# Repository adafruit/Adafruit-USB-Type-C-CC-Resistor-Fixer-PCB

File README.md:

## Adafruit USB Type C CC Resistor Fixer PCB

<a href="http://www.adafruit.com/products/6323"><br/>
Click here to purchase one from the Adafruit shop</a>

PCB files for the Adafruit USB Type C CC Resistor Fixer. 

Format is EagleCAD schematic and board layout
* https://www.adafruit.com/product/6323

### Description

Do you have any devices with USB C connections that don't seem to power or work when plugged into another USB C port? Chances are, the designers skimped a few pennies or just forgot to put in the two 5.1K CC resistors required for C-to-C connections at 5V. It can drive you batty because some computers care and some don't!

That's why we designed the Adafruit USB Type C CC Resistor Fixer, a collab between our  sunken USB socket and USB Plug breakout. It's the only product we hope we can discontinue one day, sooner rather than later! This small PCB assembly fits onto a cable or into the mis-designed port. It passes through the two data pins and the Vbus and Ground power lines, while adding the missing 5.1K resistors on the port side and a power good LED.

Note that the USB plug pinout doesn't carry the sideband wires or the high speed pins, so this is good for USB charge/sync but not for high speed or specialty protocols. If you're not sure, then it's very unlikely you need them: those products aren't going to mess up the CC resistors.

### License

Adafruit invests time and resources providing this open source design, please support Adafruit and open-source hardware by purchasing products from [Adafruit](https://www.adafruit.com)!

Designed by Limor Fried/Ladyada for Adafruit Industries.

Creative Commons Attribution/Share-Alike, all text above must be included in any redistribution. 
See license.txt for additional details.

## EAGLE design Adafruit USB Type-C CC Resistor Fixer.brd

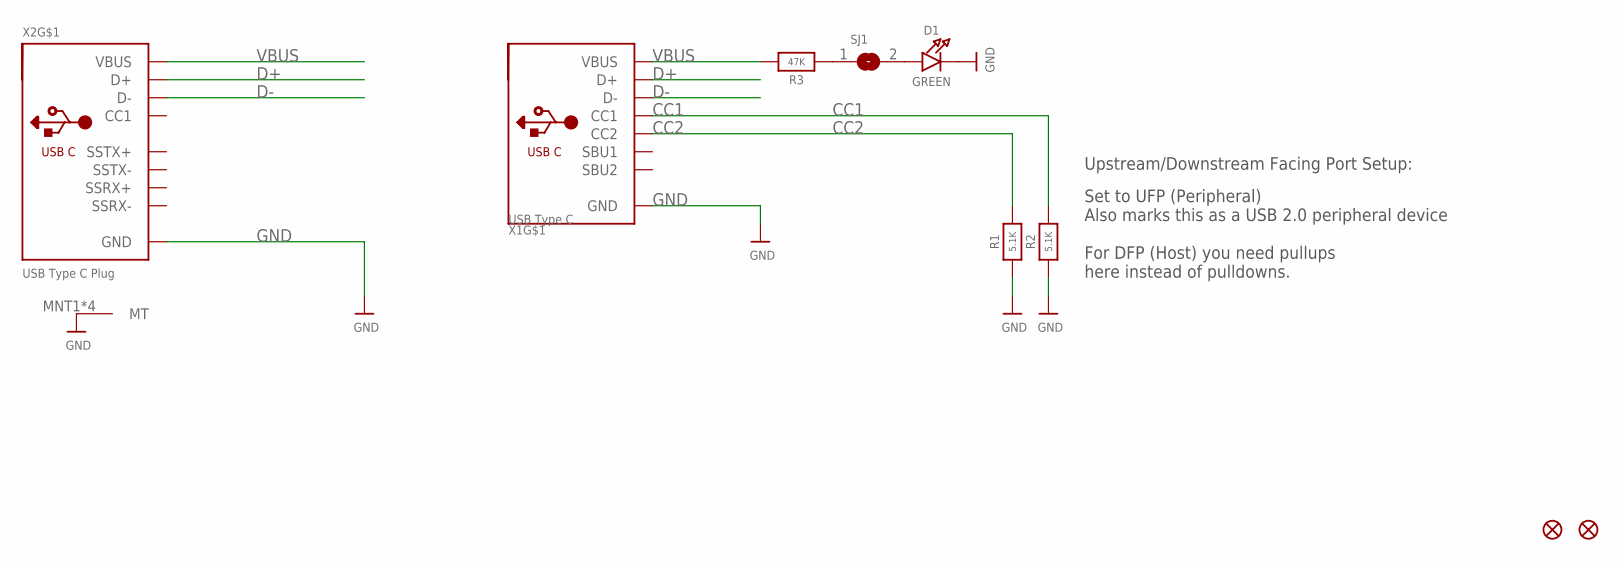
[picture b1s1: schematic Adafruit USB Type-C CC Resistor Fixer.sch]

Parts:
D1: GREEN; CHIPLED_0603_NOOUTLINE
FID1, FID2: FIDUCIAL_0.5MM
R1, R2: 5.1K; 0603-NO
R3: 47K; 0603-NO
SJ1: SOLDERJUMPERCLOSED; SOLDERJUMPER_CLOSEDWIRE
X1: USB Type C; USB_C_SINK
X2: USB Type C Plug; USB_TYPEC_PLUG_12P

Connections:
CC1: R2.2, X1.A5 (CC1)
CC2: R1.2, X1.B5 (CC2)
D+: X1.A6 (D+), X1.B6 (D+), X2.A6 (D+)
D-: X1.A7 (D-), X1.B7 (D-), X2.A7 (D-)
GND: D1.C, R1.1, R2.1, X1.A1B12 (GND), X1.B1A12 (GND), X2.A1 (GND), X2.A12 (GND), X2.B12 (GND), X2.MNT1 (MT), X2.MNT2 (MT), X2.P$1 (MT), X2.P$2 (MT)
unnamed: R3.1, SJ1.1
unnamed: D1.A, SJ1.2
VBUS: R3.2, X1.A4B9 (VBUS), X1.B4A9 (VBUS), X2.A4 (VBUS), X2.B9 (VBUS)

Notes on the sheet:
Set to UFP (Peripheral) Also marks this as a USB 2.0 peripheral device For DFP (Host) you need pullups here instead of pulldowns.
Upstream/Downstream Facing Port Setup:

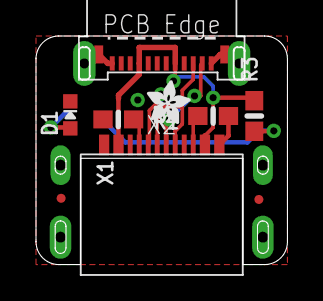
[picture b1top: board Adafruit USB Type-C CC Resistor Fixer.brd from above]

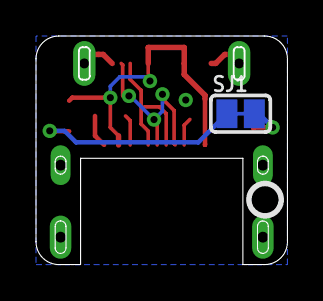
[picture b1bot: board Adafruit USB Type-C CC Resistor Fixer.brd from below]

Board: 2 copper layers, 13.9 x 12.6 mm, 14 parts (3 on the bottom side), 8 nets.

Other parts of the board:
PLABEL0: PLABEL0
PLABEL1: PLABEL1
PLABEL2: PLABEL2
U$3: ADAFRUIT_2.5MM
U$8: PCBFEAT-REV-040

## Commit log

2025-04-17 cookiecutter

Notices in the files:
parts and their libraries:
microbuilder: This work is placed in the public domain, and may be freely used for commercial and non-commercial work with the following conditions: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
